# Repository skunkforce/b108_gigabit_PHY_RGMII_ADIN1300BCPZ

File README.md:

# edgy_board number b108
This design is part of the [edgy board project](https://github.com/skunkforce/edgy_boards).

# getting started
This repository uses submodules. After cloning use the command 

```$ git submodule update --init --recursive```

to pull the submodules before opening the project with kicad. 

# Tests
Tests can be found in [TESTS.md](TESTS.md)

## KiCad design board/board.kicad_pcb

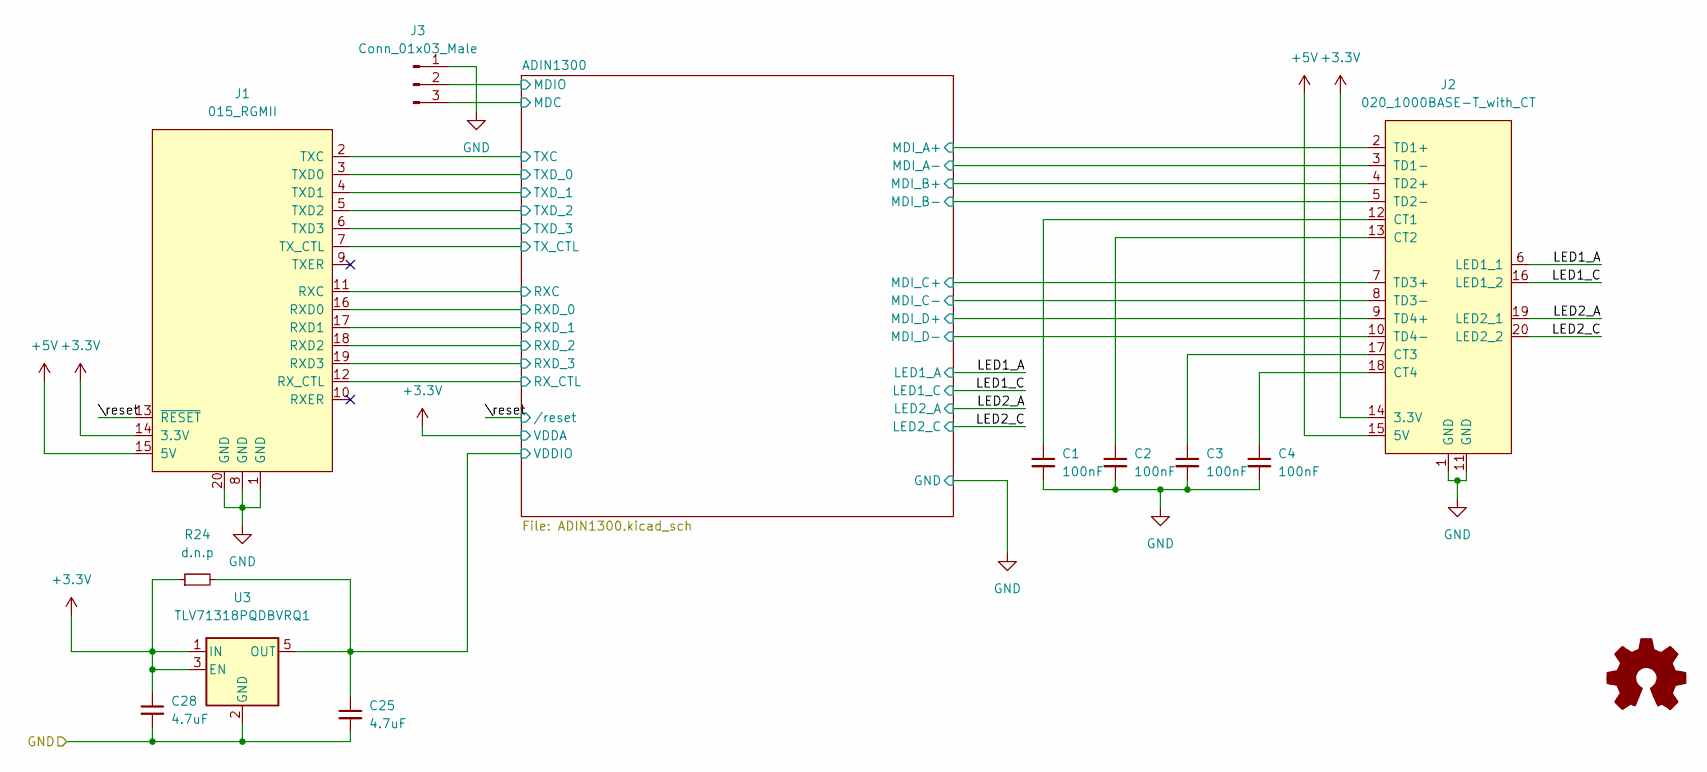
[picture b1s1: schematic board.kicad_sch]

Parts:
C1, C2, C3, C4: 100nF; C_0603_1608Metric
C25, C28: 4.7uF; C_0603_1608Metric
J1: 015_RGMII; on_edge_2x10_device
J2: 020_1000BASE-T_with_CT; on_edge_2x10_host
J3: Conn_01x03_Male; PinHeader_1x03_P2.54mm_Vertical
LOGO1: Logo_Open_Hardware_Small; OSHW-Symbol_6.7x6mm_SilkScreen
R24: d.n.p; R_0603_1608Metric
U3: TLV71318PQDBVRQ1; SOT-23-5; MPN TLV71318PQDBVRQ1; Digi-Key_PN 296-42363-1-ND

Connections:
+3.3V: C28.1, J1.14 (3.3V), J2.14 (3.3V), R24.1, U3.1 (IN), U3.3 (EN); also elsewhere on the board
+5V: J1.15 (5V), J2.15 (5V)
/ADIN1300/MDC: J3.3; also elsewhere on the board
/ADIN1300/MDIO: J3.2; also elsewhere on the board
/ADIN1300/MDI_A+: J2.2 (TD1+); also elsewhere on the board
/ADIN1300/MDI_A-: J2.3 (TD1-); also elsewhere on the board
/ADIN1300/MDI_B+: J2.4 (TD2+); also elsewhere on the board
/ADIN1300/MDI_B-: J2.5 (TD2-); also elsewhere on the board
/ADIN1300/MDI_C+: J2.7 (TD3+); also elsewhere on the board
/ADIN1300/MDI_C-: J2.8 (TD3-); also elsewhere on the board
/ADIN1300/MDI_D+: J2.9 (TD4+); also elsewhere on the board
/ADIN1300/MDI_D-: J2.10 (TD4-); also elsewhere on the board
/ADIN1300/RXC: J1.11 (RXC); also elsewhere on the board
/ADIN1300/RXD_0: J1.16 (RXD0); also elsewhere on the board
/ADIN1300/RXD_1: J1.17 (RXD1); also elsewhere on the board
/ADIN1300/RXD_2: J1.18 (RXD2); also elsewhere on the board
/ADIN1300/RXD_3: J1.19 (RXD3); also elsewhere on the board
/ADIN1300/RX_CTL: J1.12 (RX_CTL); also elsewhere on the board
/ADIN1300/TXC: J1.2 (TXC); also elsewhere on the board
/ADIN1300/TXD_0: J1.3 (TXD0); also elsewhere on the board
/ADIN1300/TXD_1: J1.4 (TXD1); also elsewhere on the board
/ADIN1300/TXD_2: J1.5 (TXD2); also elsewhere on the board
/ADIN1300/TXD_3: J1.6 (TXD3); also elsewhere on the board
/ADIN1300/TX_CTL: J1.7 (TX_CTL); also elsewhere on the board
/ADIN1300/VDDIO: C25.1, R24.2, U3.5 (OUT); also elsewhere on the board
/LED1_A: J2.6 (LED1_1); also elsewhere on the board
/LED1_C: J2.16 (LED1_2); also elsewhere on the board
/LED2_A: J2.19 (LED2_1); also elsewhere on the board
/LED2_C: J2.20 (LED2_2); also elsewhere on the board
/\reset: J1.13 (~RESET); also elsewhere on the board
GND: C1.2, C2.2, C3.2, C4.2, C25.2, C28.2, J1.1 (GND), J1.8 (GND), J1.20 (GND), J2.1 (GND), J2.11 (GND), J3.1, U3.2 (GND); also elsewhere on the board
unnamed: C1.1, J2.12 (CT1)
unnamed: C2.1, J2.13 (CT2)
unnamed: C3.1, J2.17 (CT3)
unnamed: C4.1, J2.18 (CT4)

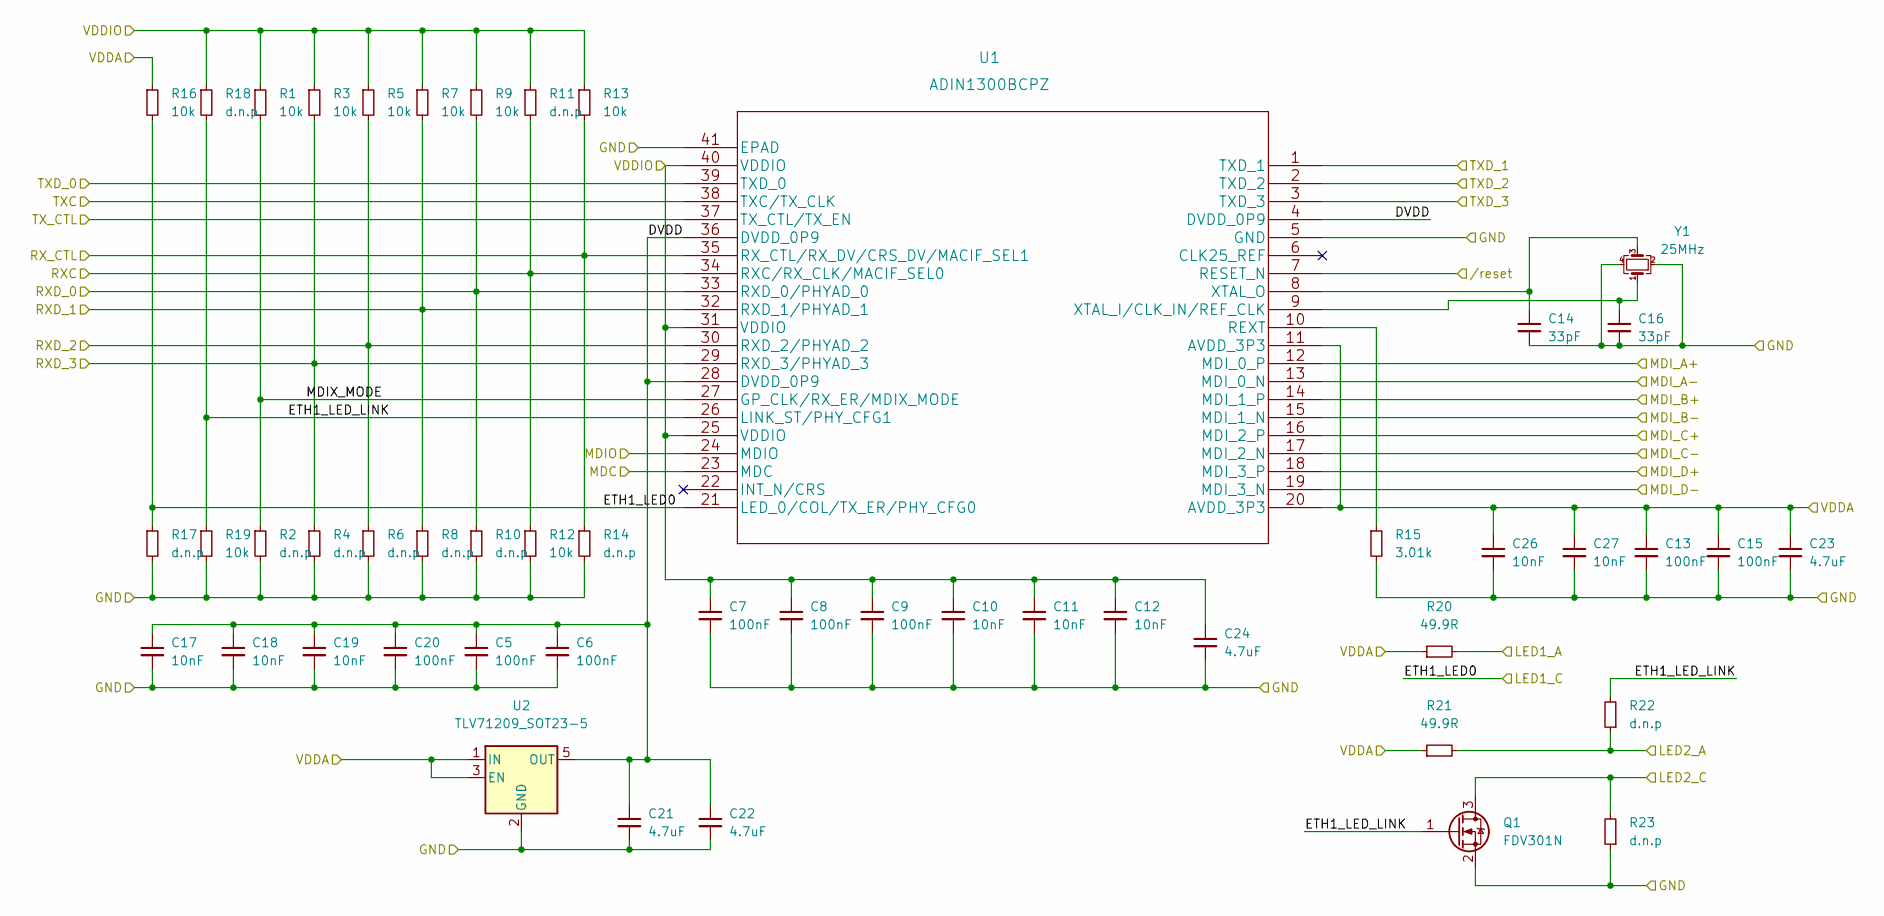
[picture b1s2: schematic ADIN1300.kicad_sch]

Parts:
C5, C6, C7, C8, C9, C13, C15, C20: 100nF; C_0603_1608Metric
C10, C11, C12, C17, C18, C19, C26, C27: 10nF; C_0603_1608Metric
C14, C16: 33pF; C_0603_1608Metric
C21, C22, C23, C24: 4.7uF; C_0603_1608Metric
Q1: FDV301N; SOT-23; MPN FDV301N; Digi-Key_PN FDV301NCT-ND
R1, R3, R5, R7, R9, R12, R13, R16, R19: 10k; R_0603_1608Metric
R2, R4, R6, R8, R10, R11, R14, R17, R18, R22, R23: d.n.p; R_0603_1608Metric
R15: 3.01k; R_0603_1608Metric
R20, R21: 49.9R; R_0603_1608Metric
U1: ADIN1300BCPZ
U2: TLV71209_SOT23-5; SOT-23-5
Y1: 25MHz; Crystal_SMD_Abracon_ABM8G-4Pin_3.2x2.5mm

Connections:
+3.3V: C13.1, C15.1, C23.1, C26.1, C27.1, R16.1, R20.1, R21.1, U1.11 (AVDD_3P3), U1.20 (AVDD_3P3), U2.1 (IN), U2.3 (EN); also elsewhere on the board
/ADIN1300/DVDD: C5.1, C6.1, C17.1, C18.1, C19.1, C20.1, C21.1, C22.1, U1.4 (DVDD_0P9), U1.28 (DVDD_0P9), U1.36 (DVDD_0P9), U2.5 (OUT)
/ADIN1300/ETH1_LED_LINK: Q1.1 (G), R18.2, R19.1, R22.2, U1.26 (LINK_ST/PHY_CFG1)
/ADIN1300/MDC: U1.23 (MDC); also elsewhere on the board
/ADIN1300/MDIO: U1.24 (MDIO); also elsewhere on the board
/ADIN1300/MDIX_MODE: R1.2, R2.1, U1.27 (GP_CLK/RX_ER/MDIX_MODE)
/ADIN1300/MDI_A+: U1.12 (MDI_0_P); also elsewhere on the board
/ADIN1300/MDI_A-: U1.13 (MDI_0_N); also elsewhere on the board
/ADIN1300/MDI_B+: U1.14 (MDI_1_P); also elsewhere on the board
/ADIN1300/MDI_B-: U1.15 (MDI_1_N); also elsewhere on the board
/ADIN1300/MDI_C+: U1.16 (MDI_2_P); also elsewhere on the board
/ADIN1300/MDI_C-: U1.17 (MDI_2_N); also elsewhere on the board
/ADIN1300/MDI_D+: U1.18 (MDI_3_P); also elsewhere on the board
/ADIN1300/MDI_D-: U1.19 (MDI_3_N); also elsewhere on the board
/ADIN1300/RXC: R11.2, R12.1, U1.34 (RXC/RX_CLK/MACIF_SEL0); also elsewhere on the board
/ADIN1300/RXD_0: R9.2, R10.1, U1.33 (RXD_0/PHYAD_0); also elsewhere on the board
/ADIN1300/RXD_1: R7.2, R8.1, U1.32 (RXD_1/PHYAD_1); also elsewhere on the board
/ADIN1300/RXD_2: R5.2, R6.1, U1.30 (RXD_2/PHYAD_2); also elsewhere on the board
/ADIN1300/RXD_3: R3.2, R4.1, U1.29 (RXD_3/PHYAD_3); also elsewhere on the board
/ADIN1300/RX_CTL: R13.2, R14.1, U1.35 (RX_CTL/RX_DV/CRS_DV/MACIF_SEL1); also elsewhere on the board
/ADIN1300/TXC: U1.38 (TXC/TX_CLK); also elsewhere on the board
/ADIN1300/TXD_0: U1.39 (TXD_0); also elsewhere on the board
/ADIN1300/TXD_1: U1.1 (TXD_1); also elsewhere on the board
/ADIN1300/TXD_2: U1.2 (TXD_2); also elsewhere on the board
/ADIN1300/TXD_3: U1.3 (TXD_3); also elsewhere on the board
/ADIN1300/TX_CTL: U1.37 (TX_CTL/TX_EN); also elsewhere on the board
/ADIN1300/VDDIO: C7.1, C8.1, C9.1, C10.1, C11.1, C12.1, C24.1, R1.1, R3.1, R5.1, R7.1, R9.1, R11.1, R13.1, R18.1, U1.25 (VDDIO), U1.31 (VDDIO), U1.40 (VDDIO); also elsewhere on the board
/LED1_A: R20.2; also elsewhere on the board
/LED1_C: R16.2, R17.1, U1.21 (LED_0/COL/TX_ER/PHY_CFG0); also elsewhere on the board
/LED2_A: R21.2, R22.1; also elsewhere on the board
/LED2_C: Q1.3 (D), R23.2; also elsewhere on the board
/\reset: U1.7 (RESET_N); also elsewhere on the board
GND: C5.2, C6.2, C7.2, C8.2, C9.2, C10.2, C11.2, C12.2, C13.2, C14.2, C15.2, C16.2, C17.2, C18.2, C19.2, C20.2, C21.2, C22.2, C23.2, C24.2, C26.2, C27.2, Q1.2 (S), R2.2, R4.2, R6.2, R8.2, R10.2, R12.2, R14.2, R15.2, R17.2, R19.2, R23.1, U1.5 (GND), U1.41 (EPAD), U2.2 (GND), Y1.2, Y1.4; also elsewhere on the board
unnamed: C14.1, U1.8 (XTAL_O), Y1.3
unnamed: C16.1, U1.9 (XTAL_I/CLK_IN/REF_CLK), Y1.1
unnamed: R15.1, U1.10 (REXT)

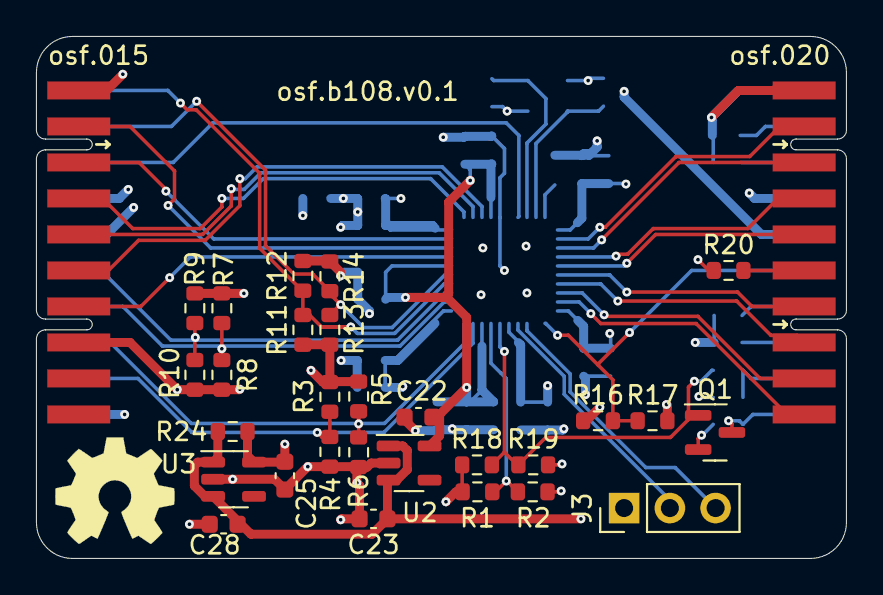
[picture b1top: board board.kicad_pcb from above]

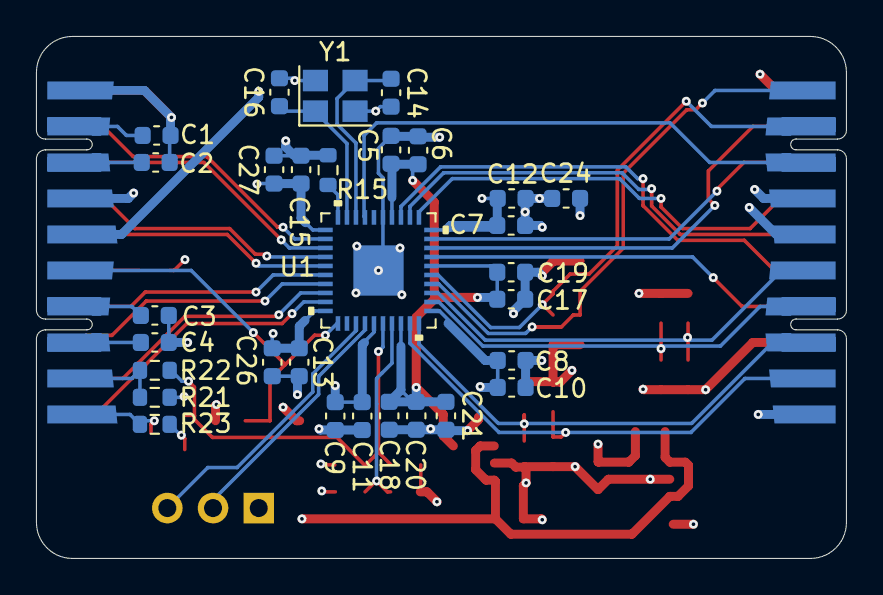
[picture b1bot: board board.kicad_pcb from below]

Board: 4 copper layers, 45.0 x 29.0 mm, 61 parts (30 on the bottom side), 41 nets.

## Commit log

2023-03-08 initial
2023-03-08 optimized EMI
2023-03-29 specified crystal frequentcy
